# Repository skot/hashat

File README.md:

WIP - don't order PCBs yet!

# hashat
A Bitcoin ASIC mining HAT for Raspberry Pi

Some of the DIY mining enthusiats from the Open Source Miners United Discord have been scheming to make a Raspberry Pi Hat! Here is what we have so far.

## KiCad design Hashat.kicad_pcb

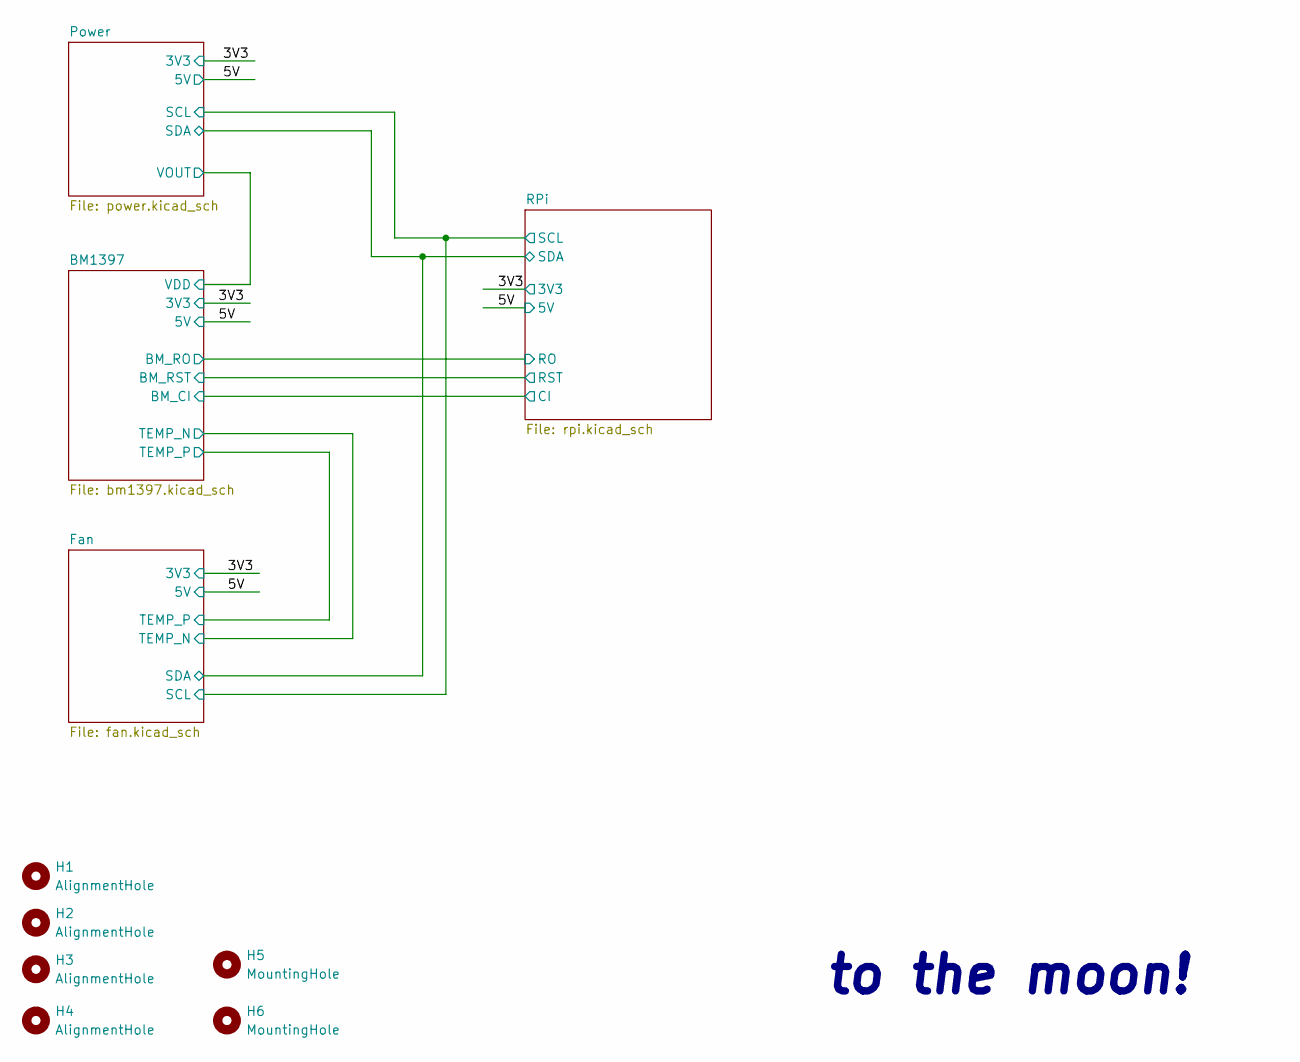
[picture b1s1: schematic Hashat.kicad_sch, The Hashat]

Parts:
H1, H2, H3, H4: AlignmentHole; MountingHole_2.2mm_M2
H5, H6: MountingHole; MountingHole_3.5mm

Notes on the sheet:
to the moon!

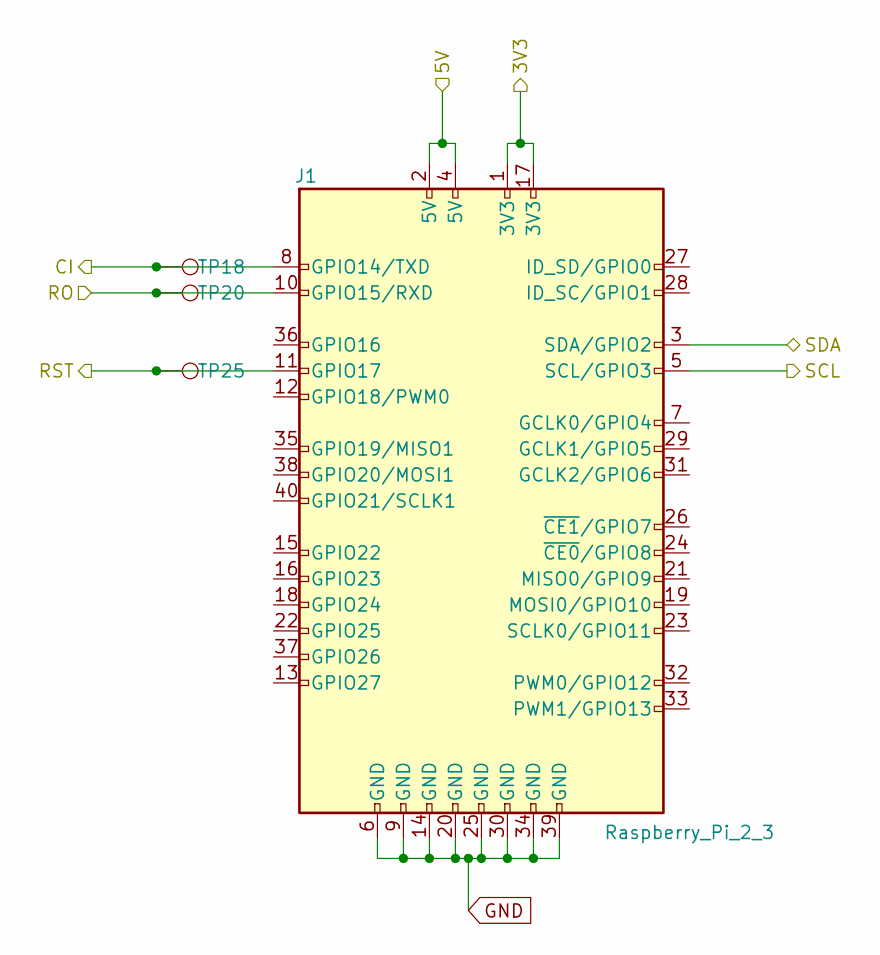
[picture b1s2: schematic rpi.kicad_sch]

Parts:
J1: Raspberry_Pi_2_3; ESQ-120-14-T-D
TP18, TP20, TP25: TestPoint; TestPoint_Pad_D1.5mm

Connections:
/3V3: J1.1 (3V3), J1.17 (3V3); also elsewhere on the board
/5V: J1.2 (5V), J1.4 (5V); also elsewhere on the board
/BM1397/BM_CI: J1.8 (GPIO14/TXD), TP18.1; also elsewhere on the board
/BM1397/BM_RO: J1.10 (GPIO15/RXD), TP20.1; also elsewhere on the board
/BM1397/BM_RST: J1.11 (GPIO17), TP25.1; also elsewhere on the board
/Fan/SCL: J1.5 (SCL/GPIO3); also elsewhere on the board
/Fan/SDA: J1.3 (SDA/GPIO2); also elsewhere on the board
GND: J1.6 (GND), J1.9 (GND), J1.14 (GND), J1.20 (GND), J1.25 (GND), J1.30 (GND), J1.34 (GND), J1.39 (GND); also elsewhere on the board

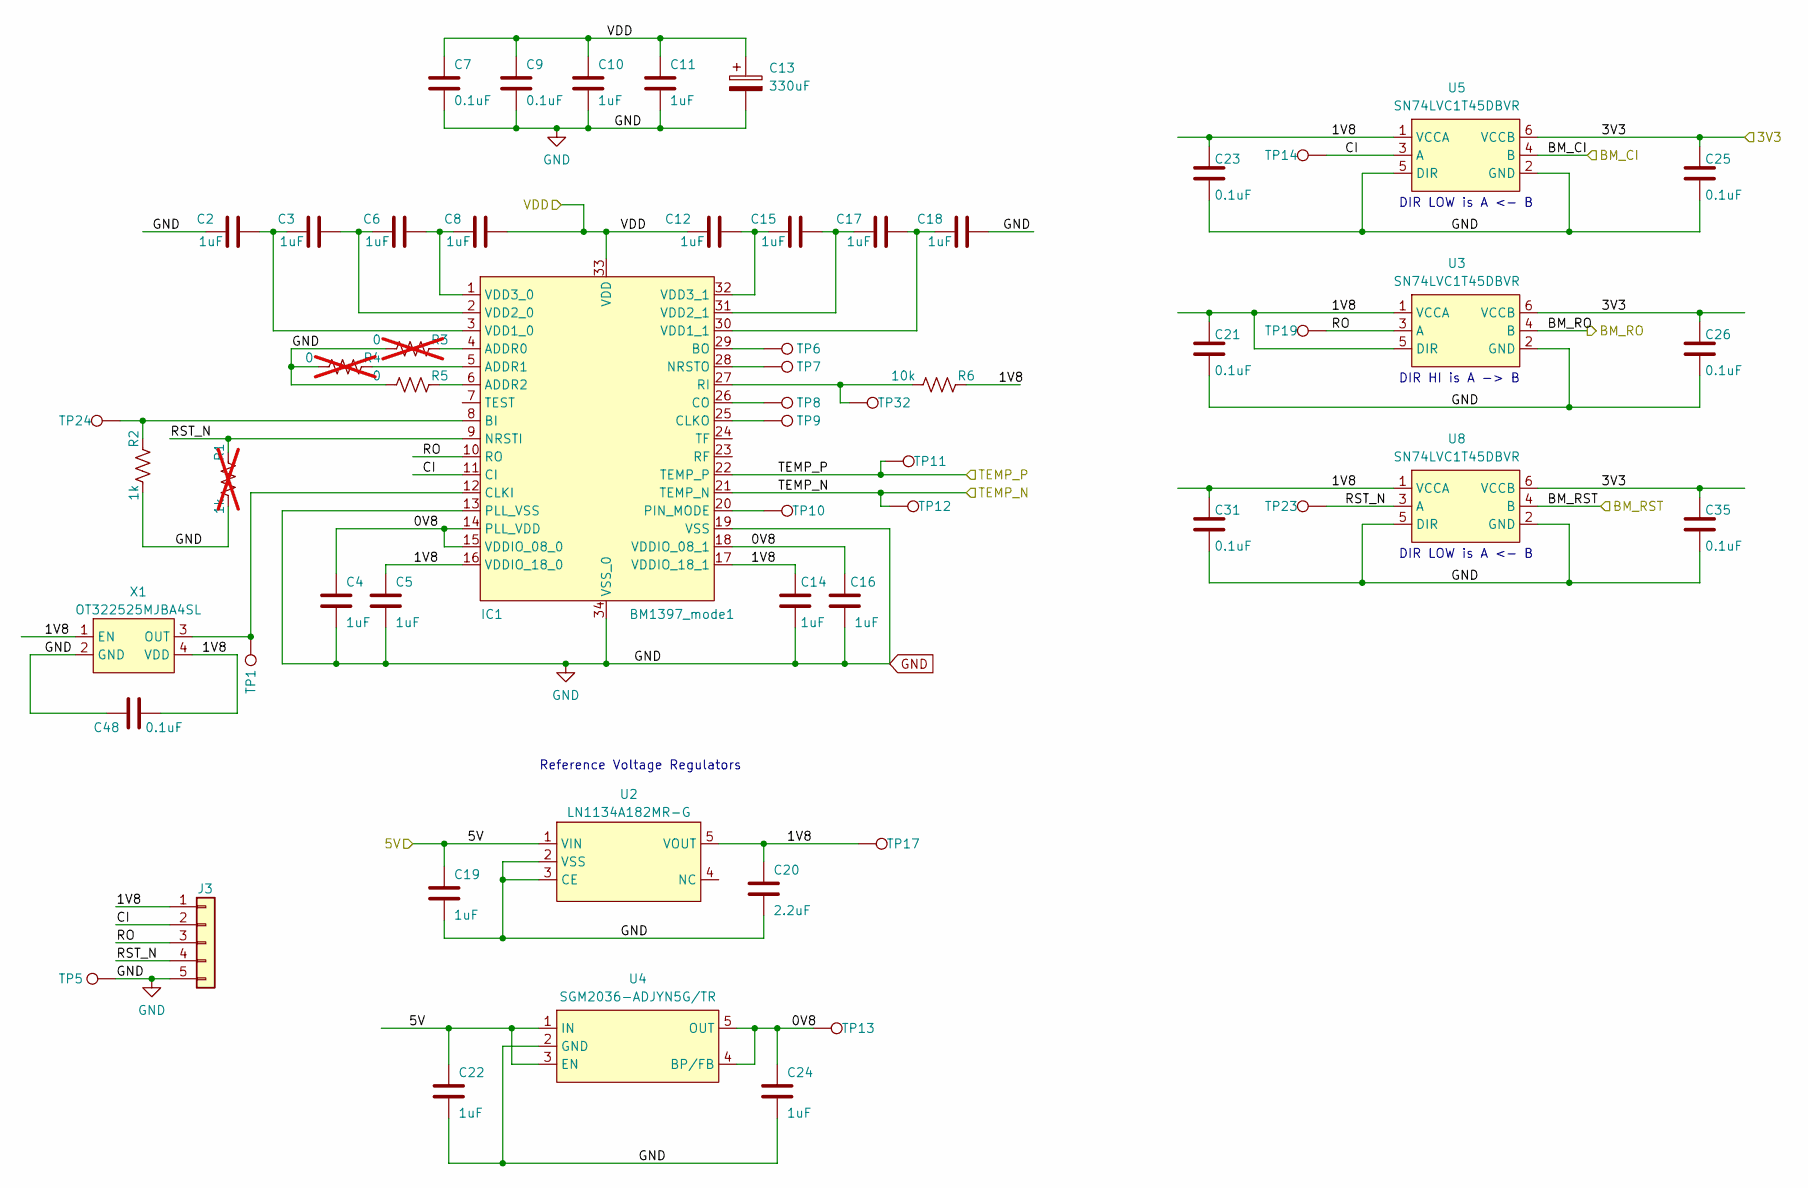
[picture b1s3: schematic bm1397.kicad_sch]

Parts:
C2, C3, C4, C5, C6, C8, C10, C11, C12, C14, C15, C16, C17, C18: 587-5514-1-ND; C_0402_1005Metric; PARTNO EMK105BJ105MV-F
C7, C9, C21, C23, C25, C26, C31, C35, C48: 311-3342-1-ND; C_0402_1005Metric; PARTNO 0402X104K100CT
C13: 330uF; CP_EIA-7343-31_Kemet-D_Pad2.25x2.55mm_HandSolder; PARTNO 293D337X9010E2TE3
C19, C22, C24: 1uF; C_0402_1005Metric; PARTNO EMK105BJ105MV-F
C20: 2.2uF; C_0402_1005Metric; PARTNO KGM05AR51A225MH
IC1: BM1397_mode1; BM1397
J3: Conn_01x05; PinHeader_1x05_P2.54mm_Vertical
R1: 1k; R_0402_1005Metric; PARTNO RT0402BRE071KL; not fitted
R2: 1k; R_0402_1005Metric; PARTNO RT0402BRE071KL
R3, R4: 0; R_0402_1005Metric; PARTNO RMCF0402ZT0R00CT-ND; not fitted
R5: 0; R_0402_1005Metric; PARTNO RMCF0402ZT0R00CT-ND
R6: 10k; R_0402_1005Metric; PARTNO RC0402JR-0710KL
TP1, TP5, TP6, TP7, TP8, TP9, TP10, TP11, TP12, TP13, TP14, TP17, TP19, TP23, TP24, TP32: TestPoint; TestPoint_Pad_D1.5mm
U2: LN1134A182MR-G; SOT-23-5_L3.0-W1.7-P0.95-LS2.8-BR; LCSC Part C141424
U3, U5, U8: SN74LVC1T45DBVR; SOT-23-6_L2.9-W1.6-P0.95-LS2.8-BR; LCSC Part C7843
U4: SGM2036-ADJYN5G/TR; SOT-23-5_L3.0-W1.7-P0.95-LS2.8-BR; LCSC Part C194594
X1: OT322525MJBA4SL; OSC-SMD_4P-L3.2-W2.5-BL; LCSC Part C669088

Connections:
/3V3: C25.1, C26.1, C35.1, U3.6 (VCCB), U5.6 (VCCB), U8.6 (VCCB); also elsewhere on the board
/5V: C19.1, C22.1, U2.1 (VIN), U4.1 (IN), U4.3 (EN); also elsewhere on the board
/BM1397/0V8: C4.1, C16.1, C24.1, IC1.14 (PLL_VDD), IC1.15 (VDDIO_08_0), IC1.18 (VDDIO_08_1), TP13.1, U4.4 (BP/FB), U4.5 (OUT)
/BM1397/1V8: C5.1, C14.1, C20.1, C21.1, C23.1, C31.1, C48.2, IC1.16 (VDDIO_18_0), IC1.17 (VDDIO_18_1), J3.1, R6.2, TP17.1, U2.5 (VOUT), U3.1 (VCCA), U3.5 (DIR), U5.1 (VCCA), U8.1 (VCCA), X1.1 (EN), X1.4 (VDD)
/BM1397/BM_CI: U5.4 (B); also elsewhere on the board
/BM1397/BM_RO: U3.4 (B); also elsewhere on the board
/BM1397/BM_RST: U8.4 (B); also elsewhere on the board
/BM1397/CI: IC1.11 (CI), J3.2, TP14.1, U5.3 (A)
/BM1397/RO: IC1.10 (RO), J3.3, TP19.1, U3.3 (A)
/BM1397/RST_N: IC1.9 (NRSTI), J3.4, R1.2, TP23.1, U8.3 (A)
/BM1397/TEMP_N: IC1.21 (TEMP_N), TP12.1; also elsewhere on the board
/BM1397/TEMP_P: IC1.22 (TEMP_P), TP11.1; also elsewhere on the board
/BM1397/VDD: C7.1, C8.2, C9.1, C10.1, C11.1, C12.1, C13.1, IC1.33 (VDD); also elsewhere on the board
GND: C2.1, C4.2, C5.2, C7.2, C9.2, C10.2, C11.2, C13.2, C14.2, C16.2, C18.2, C19.2, C20.2, C21.2, C22.2, C23.2, C24.2, C25.2, C26.2, C31.2, C35.2, C48.1, IC1.13 (PLL_VSS), IC1.19 (VSS), IC1.34 (VSS_0), J3.5, R1.1, R2.1, R3.1, R4.1, R5.1, TP5.1, U2.2 (VSS), U2.3 (CE), U3.2 (GND), U4.2 (GND), U5.2 (GND), U5.5 (DIR), U8.2 (GND), U8.5 (DIR), X1.2 (GND); also elsewhere on the board
unnamed: IC1.4 (ADDR0), R3.2
unnamed: IC1.5 (ADDR1), R4.2
unnamed: IC1.6 (ADDR2), R5.2
unnamed: IC1.8 (BI), R2.2, TP24.1
unnamed: IC1.29 (BO), TP6.1
unnamed: IC1.12 (CLKI), TP1.1, X1.3 (OUT)
unnamed: IC1.25 (CLKO), TP9.1
unnamed: IC1.26 (CO), TP8.1
unnamed: IC1.28 (NRSTO), TP7.1
unnamed: IC1.20 (PIN_MODE), TP10.1
unnamed: IC1.27 (RI), R6.1, TP32.1
unnamed: C2.2, C3.1, IC1.3 (VDD1_0)
unnamed: C17.2, C18.1, IC1.30 (VDD1_1)
unnamed: C3.2, C6.1, IC1.2 (VDD2_0)
unnamed: C15.2, C17.1, IC1.31 (VDD2_1)
unnamed: C6.2, C8.1, IC1.1 (VDD3_0)
unnamed: C12.2, C15.1, IC1.32 (VDD3_1)

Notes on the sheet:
Reference Voltage Regulators
DIR HI is A -> B
DIR LOW is A <- B

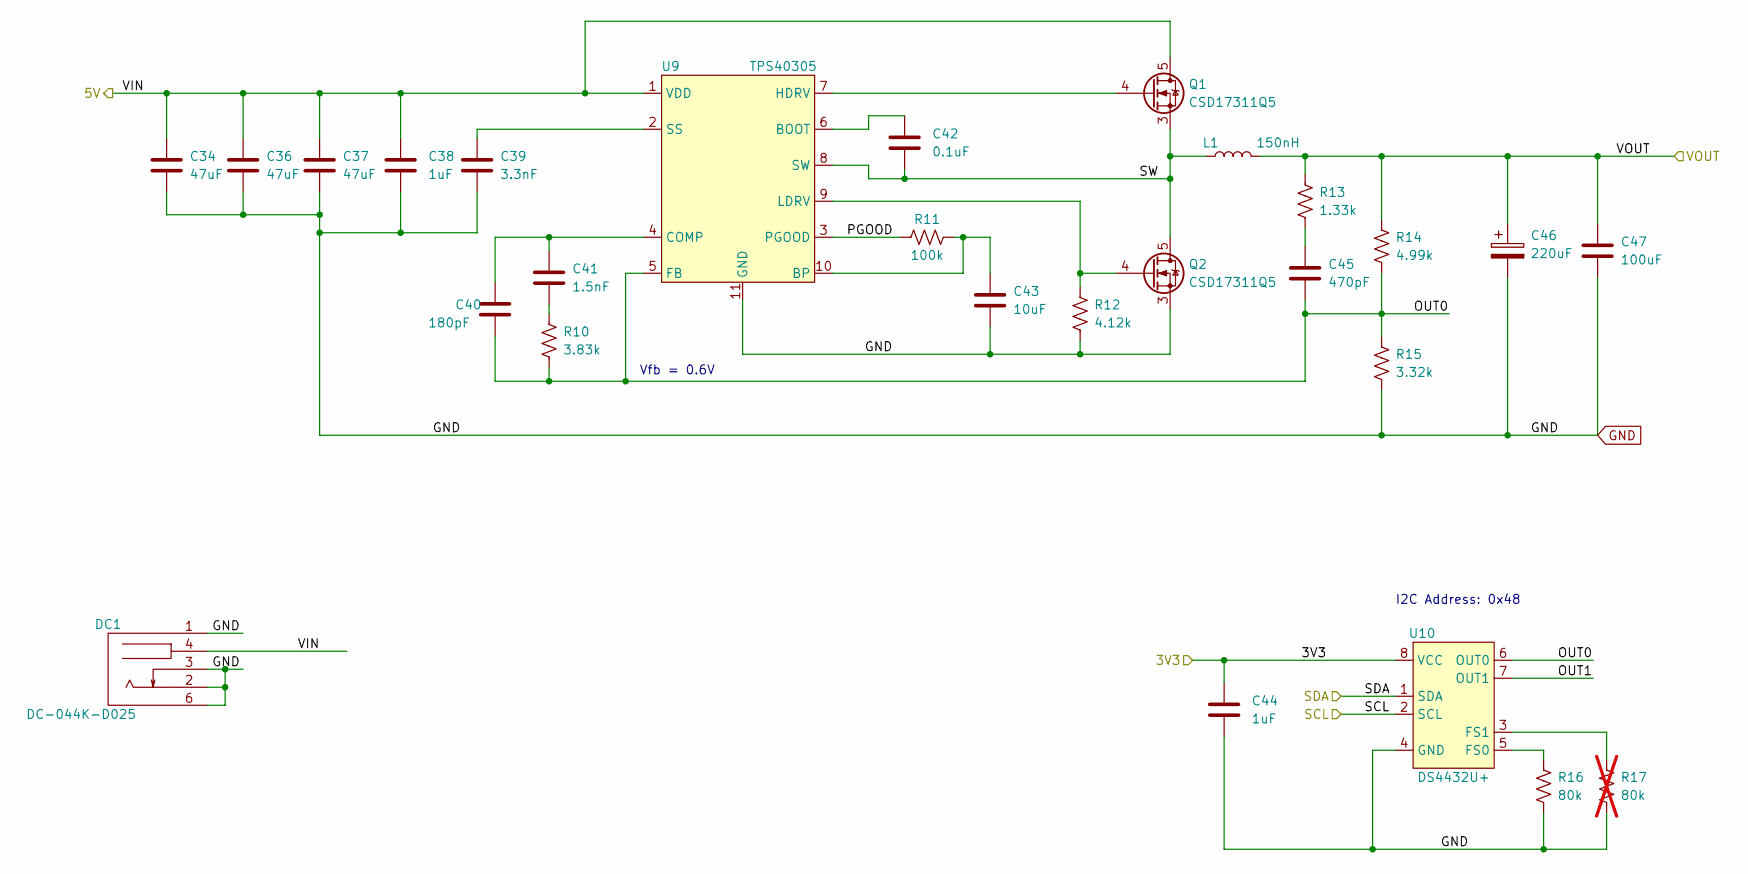
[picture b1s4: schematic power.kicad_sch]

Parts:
C34, C36, C37: 47uF; C_1210_3225Metric; PARTNO GRM32ER61C476KE15L
C38: 1uF; C_0805_2012Metric; PARTNO CL21B105KOFNNNG
C39: 3.3nF; C_0402_1005Metric; PARTNO CL05B332KB5NNNC
C40: 180pF; C_0805_2012Metric; PARTNO CC0805JRNPO9BN181
C41: 1.5nF; C_0805_2012Metric; PARTNO CC0805KRX7R9BB152
C42: 0.1uF; C_0402_1005Metric; PARTNO 0402X104K100CT
C43: 10uF; C_0805_2012Metric; PARTNO CL21A106KOQNNNE
C44: 1uF; C_0402_1005Metric; PARTNO EMK105BJ105MV-F
C45: 470pF; C_0805_2012Metric; PARTNO 0805B471K500CT
C46: 220uF; CAP_2R5TPE220MAFB; PARTNO 2R5TPE220MAFB
C47: 100uF; C_1206_3216Metric; PARTNO C3216X5R0J107M160AB
DC1: DC-044K-D025; DC-IN-TH_DC-044K-D025; LCSC Part C963204
L1: 150nH; FP1005R1-R15-R; PARTNO FP1005R1-R15-R
Q1, Q2: CSD17311Q5; PARTNO CSD17311Q5; LCSC Part C139640
R10: 3.83k; R_0402_1005Metric; PARTNO RC0402FR-073K83L
R11: 100k; R_0402_1005Metric; PARTNO RC0402JR-07100KL
R12: 4.12k; R_0402_1005Metric; PARTNO RMCF0402FT4K12
R13: 1.33k; R_0402_1005Metric; PARTNO RC0402FR-071K33L
R14: 4.99k; R_0402_1005Metric; PARTNO RC0402FR-074K99L
R15: 3.32k; R_0402_1005Metric; PARTNO RC0402FR-073K32L
R16: 80k; R_0402_1005Metric; PARTNO RC0402FR-0780K6L
R17: 80k; R_0402_1005Metric; PARTNO RC0402FR-0780K6L; not fitted
U9: TPS40305; PARTNO TPS40305DRCR; LCSC Part C140285
U10: DS4432U+; TSSOP-8_3x3mm_P0.65mm; PARTNO DS4432U+; LCSC Part C2679620

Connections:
/3V3: C44.1, U10.8 (VCC); also elsewhere on the board
/5V: C34.1, C36.1, C37.1, C38.1, DC1.4, Q1.5 (D), U9.1 (VDD); also elsewhere on the board
/BM1397/VDD: C46.1, C47.1, L1.2, R13.1, R14.1; also elsewhere on the board
/Fan/SCL: U10.2 (SCL); also elsewhere on the board
/Fan/SDA: U10.1 (SDA); also elsewhere on the board
/Power/OUT0: C40.2, C45.2, R10.2, R14.2, R15.1, U9.5 (FB), U10.6 (OUT0)
/Power/OUT1: U10.7 (OUT1)
/Power/PGOOD: R11.1, U9.3 (PGOOD)
/Power/SW: C42.2, L1.1, Q1.1, Q1.2, Q1.3 (S), Q2.5 (D), U9.8 (SW)
GND: C34.2, C36.2, C37.2, C38.2, C39.2, C43.2, C44.2, C46.2, C47.2, DC1.1, DC1.2, DC1.3, DC1.6, Q2.1, Q2.2, Q2.3 (S), R12.2, R15.2, R16.2, R17.2, U9.11 (GND), U10.4 (GND); also elsewhere on the board
unnamed: C41.2, R10.1
unnamed: C45.1, R13.2
unnamed: Q1.4 (G), U9.7 (HDRV)
unnamed: Q2.4 (G), R12.1, U9.9 (LDRV)
unnamed: C42.1, U9.6 (BOOT)
unnamed: C43.1, R11.2, U9.10 (BP)
unnamed: C40.1, C41.1, U9.4 (COMP)
unnamed: C39.1, U9.2 (SS)
unnamed: R16.1, U10.5 (FS0)
unnamed: R17.1, U10.3 (FS1)

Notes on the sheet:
Vfb = 0.6V
I2C Address: 0x48

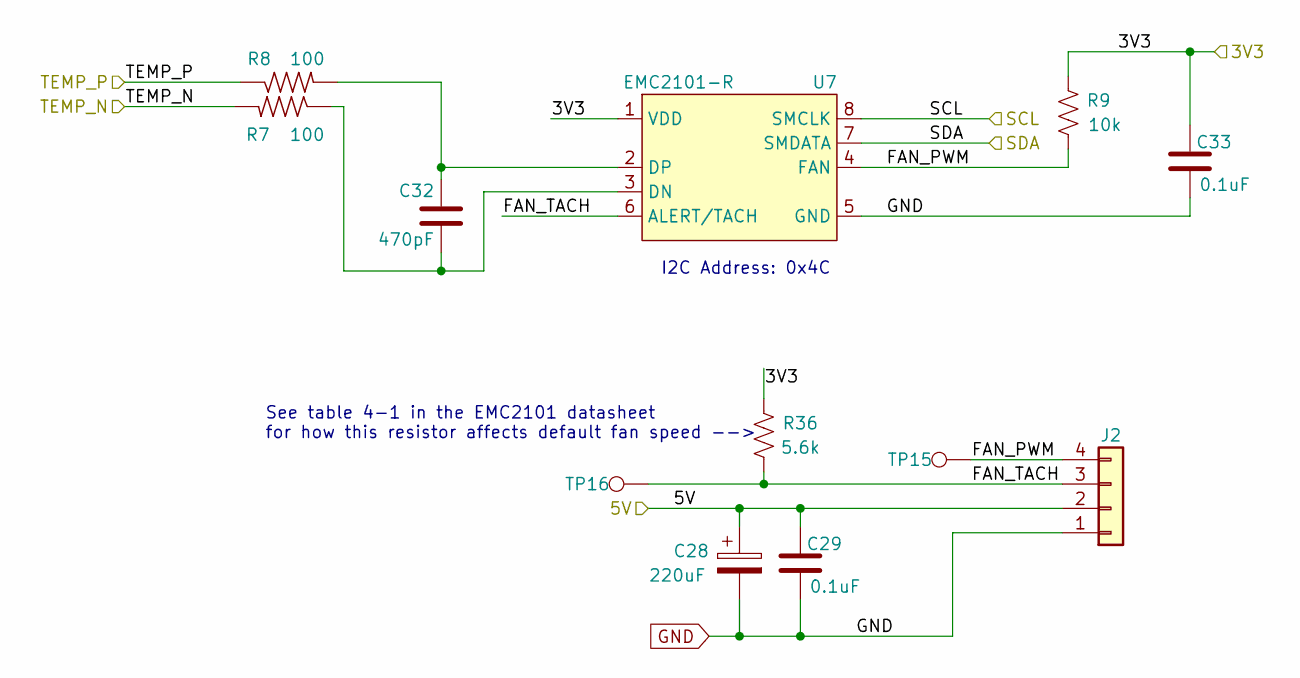
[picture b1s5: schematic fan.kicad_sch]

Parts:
C28: 220uF; CP_Elec_6.3x7.7; PARTNO 865080345012
C29, C33: 311-3342-1-ND; C_0402_1005Metric; PARTNO 0402X104K100CT
C32: 470pF; C_0402_1005Metric; PARTNO CL05B471KB5NNNC
J2: Conn_01x04; PinHeader_1x04_P2.54mm_Vertical
R7, R8: 100; R_0402_1005Metric; PARTNO RMCF0402FT100R
R9: 10k; R_0402_1005Metric; PARTNO RC0402JR-0710KL
R36: 5.6k; R_0402_1005Metric; PARTNO RC0402FR-135K6L
TP15, TP16: TestPoint; TestPoint_Pad_D1.5mm
U7: EMC2101-R; TSSOP-8_3x3mm_P0.65mm; PARTNO EMC2101-R-ACZL-TR; LCSC Part C626968

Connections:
/3V3: C33.1, R9.2, R36.2, U7.1 (VDD); also elsewhere on the board
/5V: C28.1, C29.1, J2.2; also elsewhere on the board
/BM1397/TEMP_N: R7.2; also elsewhere on the board
/BM1397/TEMP_P: R8.1; also elsewhere on the board
/Fan/FAN_PWM: J2.4, R9.1, TP15.1, U7.4 (FAN)
/Fan/FAN_TACH: J2.3, R36.1, TP16.1, U7.6 (ALERT/TACH)
/Fan/SCL: U7.8 (SMCLK); also elsewhere on the board
/Fan/SDA: U7.7 (SMDATA); also elsewhere on the board
GND: C28.2, C29.2, C33.2, J2.1, U7.5 (GND); also elsewhere on the board
unnamed: C32.2, R7.1, U7.3 (DN)
unnamed: C32.1, R8.2, U7.2 (DP)

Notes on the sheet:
See table 4-1 in the EMC2101 datasheet for how this resistor affects default fan speed -->
I2C Address: 0x4C

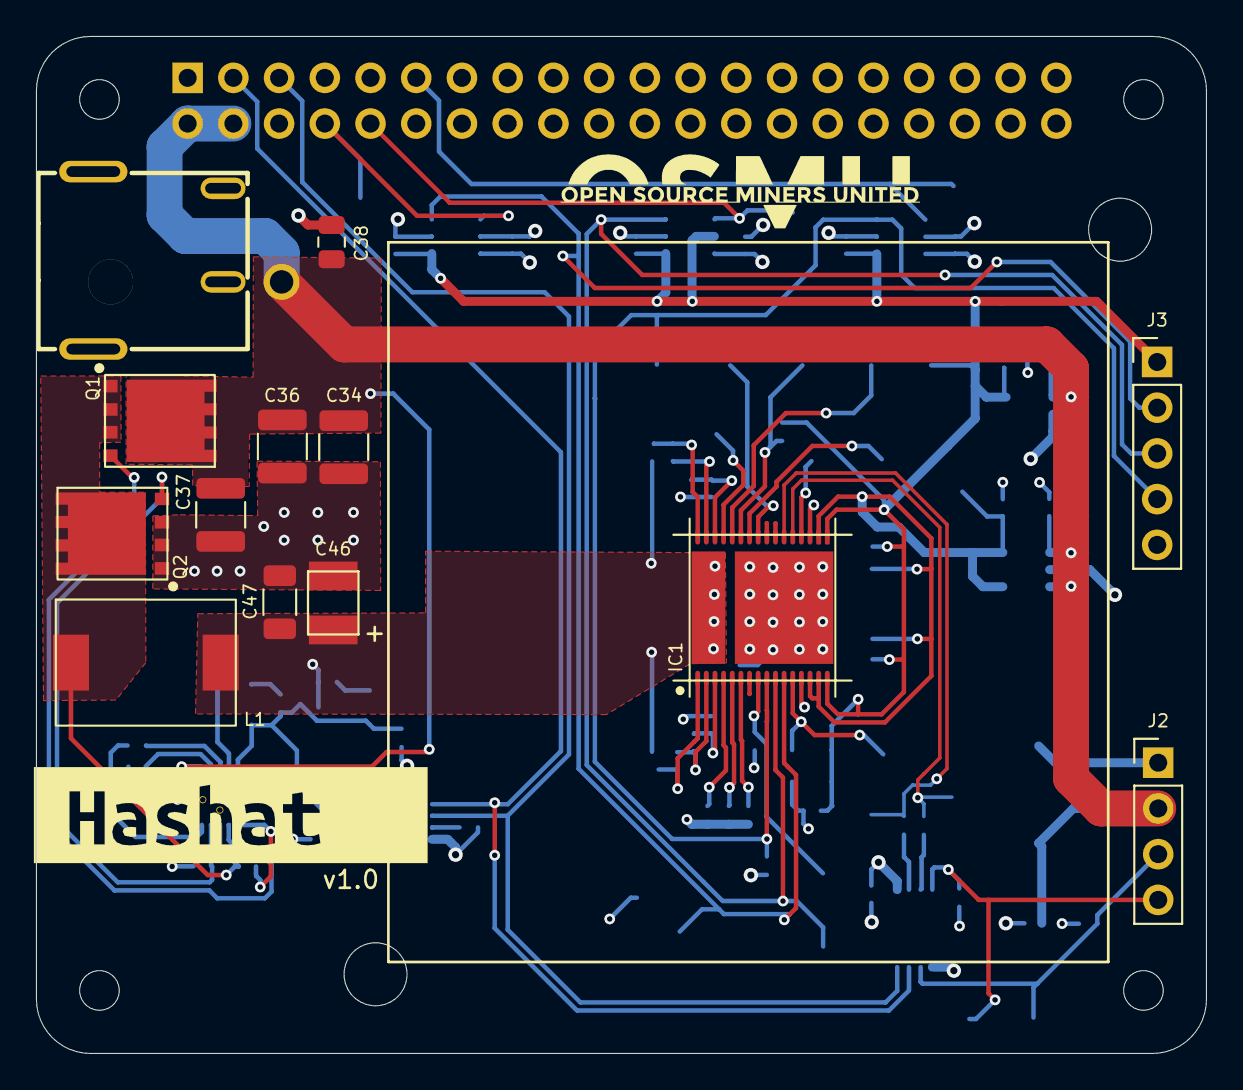
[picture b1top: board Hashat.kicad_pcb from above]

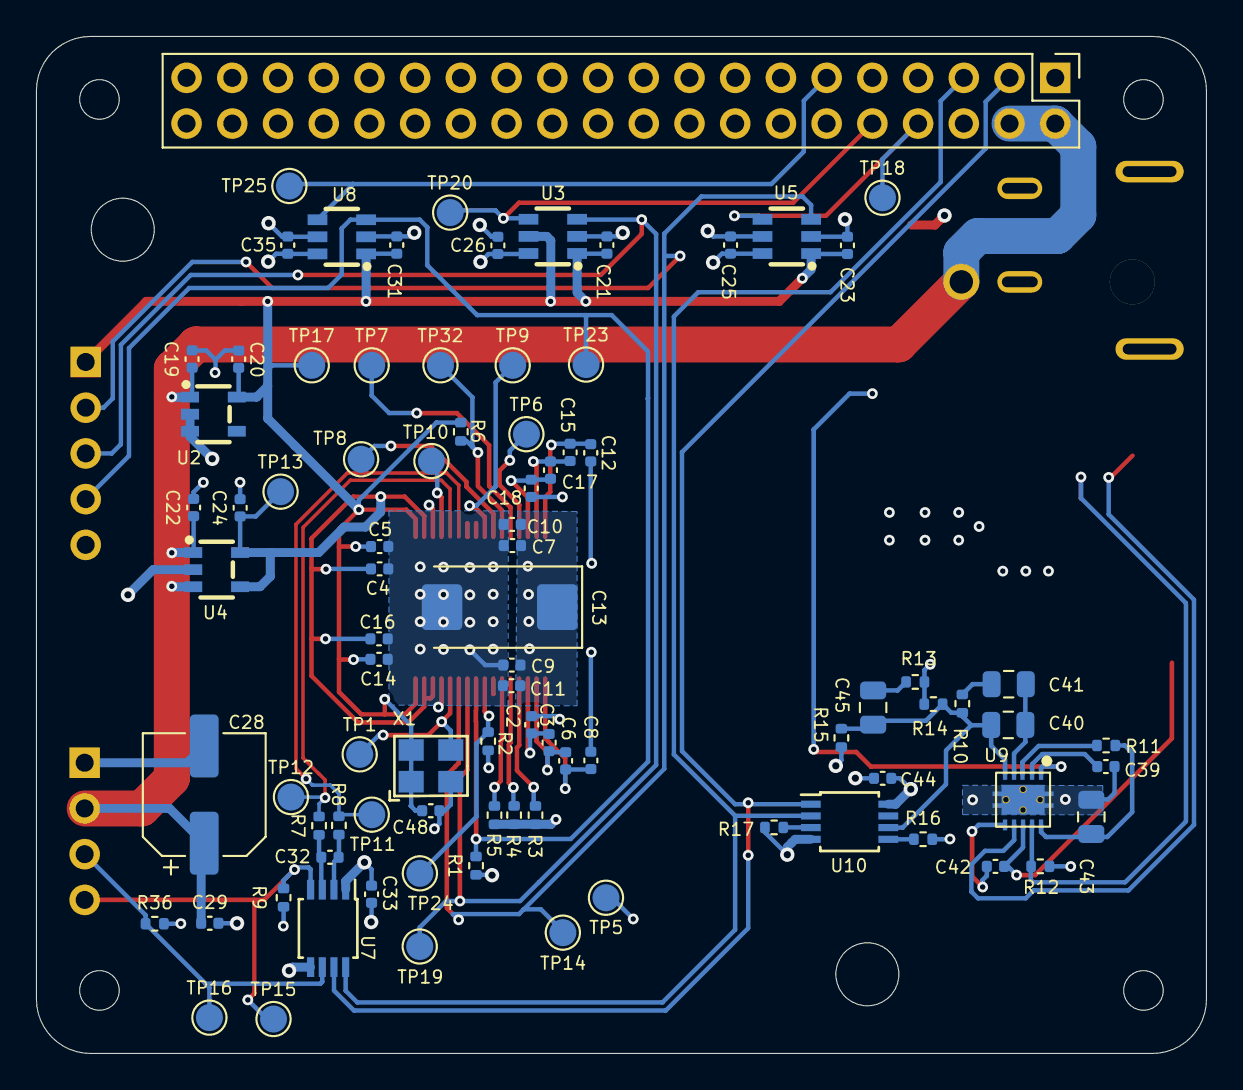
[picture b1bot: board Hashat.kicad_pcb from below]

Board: 4 copper layers, 65.0 x 56.5 mm, 108 parts (88 on the bottom side), 50 nets.

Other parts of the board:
kibuzzard-64828601: G***; kibuzzard-64828601

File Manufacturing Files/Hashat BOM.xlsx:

Qty | Ref Des | Value | DK | PARTNO | DNP
18 | C2, C3, C4, C5, C6, C8, C10, C11, C12, C14, C15, C16, C17, C18, C19, C22, C24, 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 | 1uF | 587-5514-1-ND | EMK105BJ105MV-F
12 | C7, C9, C21, C23, C25, C26, C29, C31, C33, C35, C42, C48 | 0.1uF | 1292-1639-1-ND | 0402X104K100CT
1 | C13 | 330uF | 718-1028-1-ND | 293D337X9010E2TE3
1 | C20 | 2.2uF | 478-KGM05AR51A225MHCT-ND | KGM05AR51A225MH
1 | C28 | 220uF | 732-8422-1-ND | 865080345012
1 | C32 | 470pF | 1276-1566-1-ND | CL05B471KB5NNNC
3 | C34, C36, C37 | 47uF | 490-6539-1-ND | GRM32ER61C476KE15L
1 | C38 | 1uF | 1276-6471-1-ND | CL21B105KOFNNNG
1 | C39 | 3.3nF | 1276-1552-1-ND | CL05B332KB5NNNC
1 | C40 | 180pF | 311-1114-1-ND | CC0805JRNPO9BN181
1 | C41 | 1.5nF | 311-1128-1-ND | CC0805KRX7R9BB152
1 | C43 | 10uF | 1276-1096-1-ND | CL21A106KOQNNNE
1 | C45 | 470pF | 1292-1580-1-ND | 0805B471K500CT
1 | C46 | 220uF | P16200CT-ND | 2R5TPE220MAFB
1 | C47 | 100uF | 445-6008-1-ND | C3216X5R0J107M160AB
1 | DC1 | DC-044K-D025
1 | IC1 | BM1397_mode1
1 | J1 | Raspberry_Pi_2_3
1 | J2 | Conn_01x04
1 | J3 | Conn_01x05
1 | L1 | 150nH | 513-1568-1-ND | FP1005R1-R15-R
2 | Q1, Q2 | CSD17311Q5 | 296-27625-1-ND | CSD17311Q5
1 | R1 | 1k | YAG2306CT-ND | RT0402BRE071KL | DNP
1 | R2 | 1k | YAG2306CT-ND | RT0402BRE071KL
2 | R3, R4 | 0 | RMCF0402ZT0R00 | RMCF0402ZT0R00CT-ND | DNP
1 | R5 | 0 | RMCF0402ZT0R00 | RMCF0402ZT0R00CT-ND
2 | R6, R9 | 10k | 311-10KJRCT-ND | RC0402JR-0710KL
2 | R7, R8 | 100 | RMCF0402FT100RCT-ND | RMCF0402FT100R
1 | R10 | 3.83k | 311-3.83KLRCT-ND | RC0402FR-073K83L
1 | R11 | 100k | 311-100KJRCT-ND | RC0402JR-07100KL
1 | R12 | 4.12k | RMCF0402FT4K12CT-ND | RMCF0402FT4K12
1 | R13 | 1.33k | 311-1.33KLRCT-ND | RC0402FR-071K33L
1 | R14 | 4.99k | 311-4.99KLRCT-ND | RC0402FR-074K99L
1 | R15 | 3.32k | 311-3.32KLRCT-ND | RC0402FR-073K32L
1 | R16 | 80k | 311-80.6KLRCT-ND | RC0402FR-0780K6L
1 | R17 | 80k | 311-80.6KLRCT-ND | RC0402FR-0780K6L | DNP
1 | R36 | 5.6k | 13-RC0402FR-135K6LCT-ND | RC0402FR-135K6L
1 | U2 | LN1134A182MR-G
3 | U3, U5, U8 | SN74LVC1T45DBVR
1 | U4 | SGM2036-ADJYN5G/TR
1 | U7 | EMC2101-R | EMC2101-R-ACZL-CT-ND | EMC2101-R-ACZL-TR
1 | U9 | TPS40305 | 296-37445-1-ND | TPS40305DRCR
1 | U10 | DS4432U+ | DS4432U+-ND | DS4432U+
1 | X1 | OT322525MJBA4SL

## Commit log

2023-04-22 initial import
2023-04-22 Added some placeholder sheets
2023-04-22 moved over a lot of schematic from the bitaxe
2023-04-22 more schematic
2023-04-22 more schematic. added the barrel power connector
2023-04-22 removed the camera/display cutouts from the edge cuts
2023-04-22 cleared up some part reference designator madness
2023-04-22 swapped out the VCCIO LDOs for some LCSC versions
2023-04-22 added 4 discrete level shifters with LCSC stock
2023-04-22 swapped 25MHz Osc for LCSC model
2023-04-22 matched up layout ref with schematic
2023-04-22 cleanup. added LCSC fan connector
2023-04-23 started on new LM5085 based buck design
2023-04-23 added webench design docs
2023-04-27 cleanup level shifters. LCRC inductor for buck
2023-05-02 fully removed BI (and pulled down at the BM1397)
2023-05-16 adding 3D models. lots of placement. a little routing started
2023-05-16 some more placing
2023-06-07 more routing
2023-06-08 pretty much all the signals are routed
2023-06-08 finished routing
2023-06-08 got the silkscreen refdes all placed
2023-06-09 added sweet graphics
2023-06-09 added TPS40305 3d, and Hashat render
2023-06-09 cleanup, add OSMU logos
2023-06-09 added initial BOM
2023-06-09 export gerbers and stencil files
2023-06-09 trace massaging
